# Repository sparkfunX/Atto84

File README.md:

# SparkX Atto84

The Atto84 is an Arduino compatible ATtiny84 breakout pre-programmed with the [Micronucleus V-USB bootloader](https://github.com/micronucleus/micronucleus). The Atto84 Arduino board profile is built around v1.1.5 of SpenceKonde's excellent [ATTinyCore](https://github.com/SpenceKonde/ATTinyCore). 
<br><br>
You can buy one [here](https://sparkle.sparkfun.com/sparkle/storefront_products/14804)!

Documentation
--------------
* **[Hookup Guide](https://learn.sparkfun.com/tutorials/atto84-hookup-guide)** - Basic hookup guide for the Atto84.

License Information
-------------------

This product is _**open source**_! 

Please review the LICENSE.md file for license information. 

If you have any questions or concerns on licensing, please contact techsupport@sparkfun.com.

Distributed as-is; no warranty is given.

- Your friends at SparkFun.

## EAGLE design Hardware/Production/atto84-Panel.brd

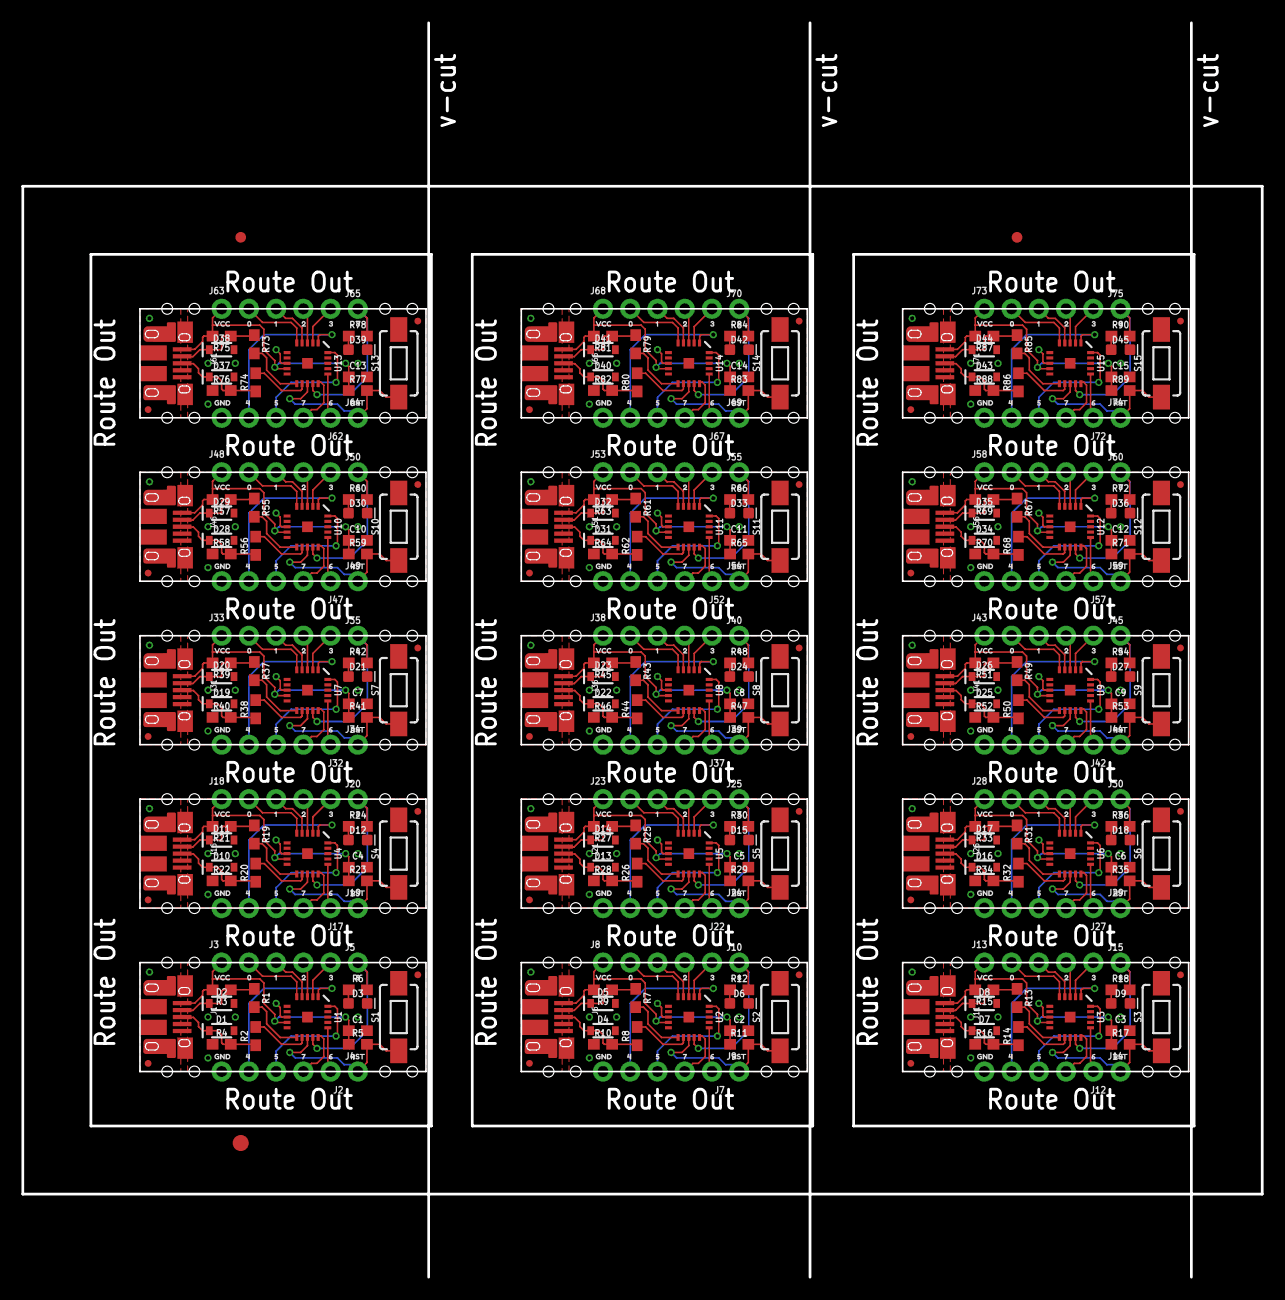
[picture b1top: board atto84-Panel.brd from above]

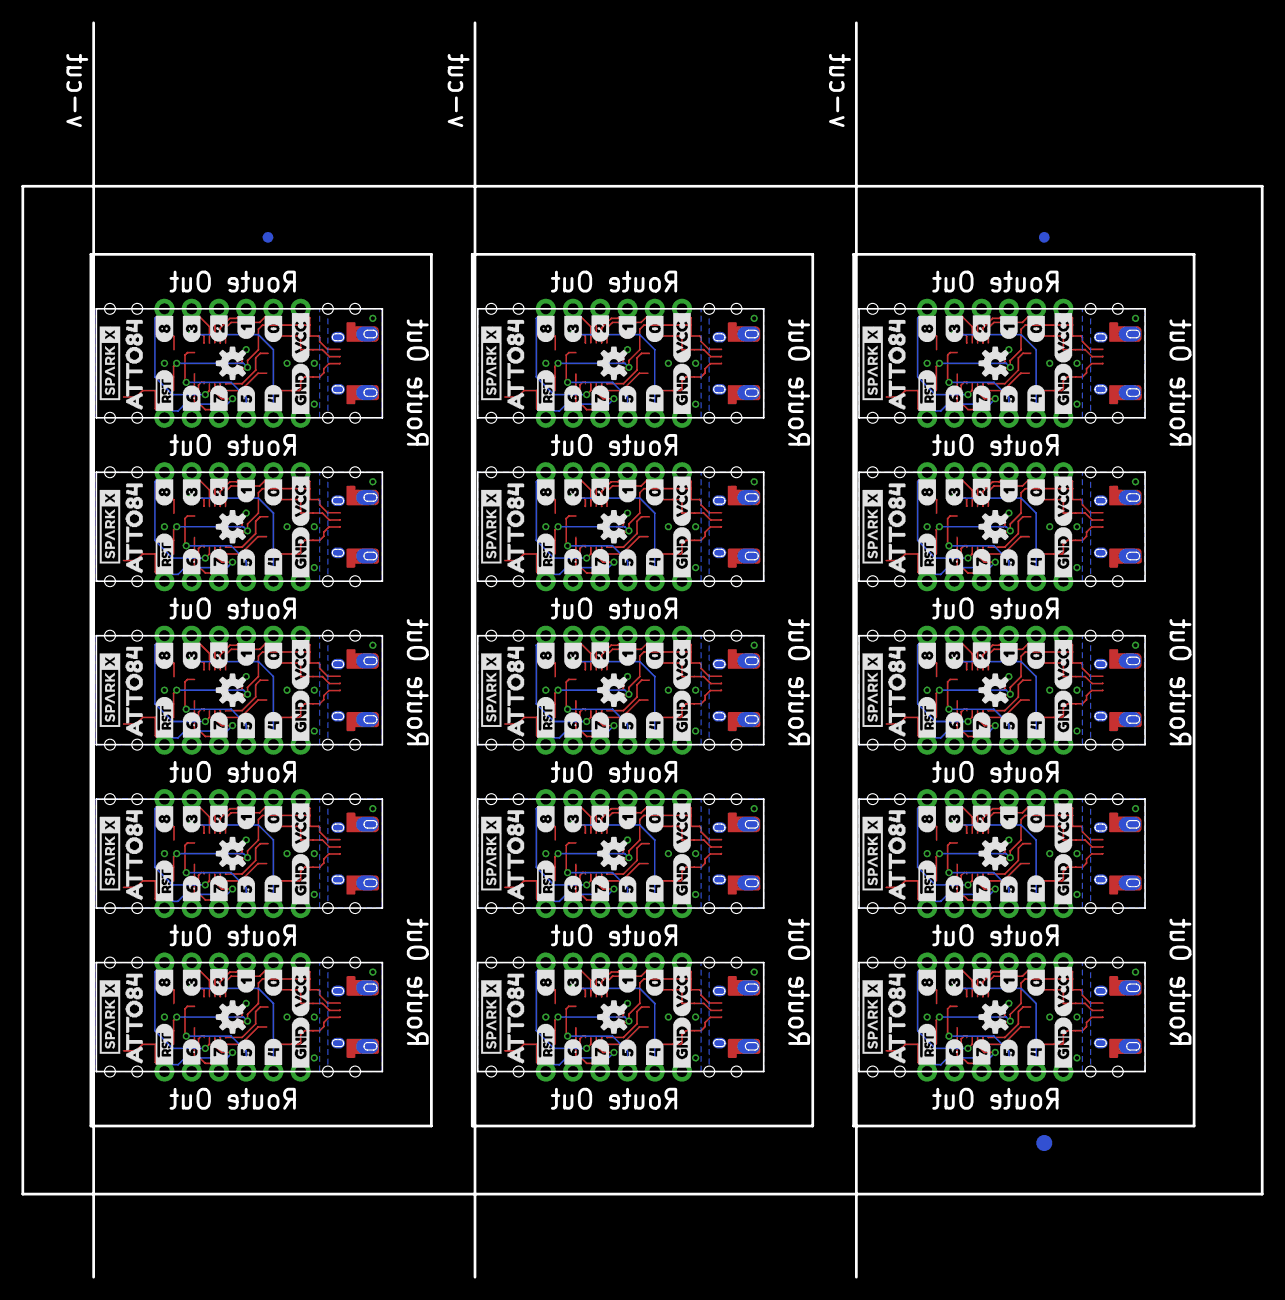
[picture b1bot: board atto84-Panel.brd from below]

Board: 2 copper layers, 115.6 x 94.0 mm, 696 parts (228 on the bottom side), 270 nets.

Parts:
C1, C2, C3, C4, C5, C6, C7, C8, C9, C10, C11, C12, C13, C14, C15: 0.1uF; 0603
D1, D2, D4, D5, D7, D8, D10, D11, D13, D14, D16, D17, D19, D20, D22, D23, D25, D26, D28, D29, D31, D32, D34, D35, D37, D38, D40, D41, D43, D44: 3.6V; SOD-323
D3, D6, D9, D12, D15, D18, D21, D24, D27, D30, D33, D36, D39, D42, D45: BLUE; LED-0603
E$1, E$2, E$3, E$4: FIDUCIAL-1X2
E$5, E$6: FIDUCIAL-1.5X3
FD1, FD2, FD3, FD4, FD5, FD6, FD7, FD8, FD9, FD10, FD11, FD12, FD13, FD14, FD15, FD16, FD17, FD18, FD19, FD20, FD21, FD22, FD23, FD24, FD25, FD26, FD27, FD28, FD29, FD30: FIDUCIALUFIDUCIAL; FIDUCIAL-MICRO
J1, J6, J11, J16, J21, J26, J31, J36, J41, J46, J51, J56, J61, J66, J71: USB-MICROB-PTH-MILL
J2, J3, J7, J8, J12, J13, J17, J18, J22, J23, J27, J28, J32, J33, J37, J38, J42, J43, J47, J48, J52, J53, J57, J58, J62, J63, J67, J68, J72, J73: 1X05_NO_SILK
J4, J5, J9, J10, J14, J15, J19, J20, J24, J25, J29, J30, J34, J35, J39, J40, J44, J45, J49, J50, J54, J55, J59, J60, J64, J65, J69, J70, J74, J75: 1X01_NO_SILK
R1, R2, R7, R8, R13, R14, R19, R20, R25, R26, R31, R32, R37, R38, R43, R44, R49, R50, R55, R56, R61, R62, R67, R68, R73, R74, R79, R80, R85, R86: 68OHM-0603-1/10W-1%; 0603
R3, R9, R15, R21, R27, R33, R39, R45, R51, R57, R63, R69, R75, R81, R87: 1.5k; 0603
R4, R10, R16, R22, R28, R34, R40, R46, R52, R58, R64, R70, R76, R82, R88: 1M; 0603
R5, R11, R17, R23, R29, R35, R41, R47, R53, R59, R65, R71, R77, R83, R89: 10k; 0603
R6, R12, R18, R24, R30, R36, R42, R48, R54, R60, R66, R72, R78, R84, R90: 1k; 0603
S1, S2, S3, S4, S5, S6, S7, S8, S9, S10, S11, S12, S13, S14, S15: TACTILE_SWITCH_SMD_6.0X3.5MM
U1, U2, U3, U4, U5, U6, U7, U8, U9, U10, U11, U12, U13, U14, U15: ATTINY84ATTINY84-20MU; QFN20
U$1, U$28, U$55, U$82, U$109, U$136, U$163, U$190, U$217, U$244, U$271, U$298, U$325, U$352, U$379: 00
U$2, U$29, U$56, U$83, U$110, U$137, U$164, U$191, U$218, U$245, U$272, U$299, U$326, U$353, U$380: 11
U$3, U$30, U$57, U$84, U$111, U$138, U$165, U$192, U$219, U$246, U$273, U$300, U$327, U$354, U$381: 22
U$4, U$31, U$58, U$85, U$112, U$139, U$166, U$193, U$220, U$247, U$274, U$301, U$328, U$355, U$382: 33
U$5, U$32, U$59, U$86, U$113, U$140, U$167, U$194, U$221, U$248, U$275, U$302, U$329, U$356, U$383: 44
U$6, U$33, U$60, U$87, U$114, U$141, U$168, U$195, U$222, U$249, U$276, U$303, U$330, U$357, U$384: 55
U$7, U$34, U$61, U$88, U$115, U$142, U$169, U$196, U$223, U$250, U$277, U$304, U$331, U$358, U$385: 66
U$8, U$35, U$62, U$89, U$116, U$143, U$170, U$197, U$224, U$251, U$278, U$305, U$332, U$359, U$386: 77
U$9, U$36, U$63, U$90, U$117, U$144, U$171, U$198, U$225, U$252, U$279, U$306, U$333, U$360, U$387: RST8
U$10, U$37, U$64, U$91, U$118, U$145, U$172, U$199, U$226, U$253, U$280, U$307, U$334, U$361, U$388: VCC10
U$11, U$38, U$65, U$92, U$119, U$146, U$173, U$200, U$227, U$254, U$281, U$308, U$335, U$362, U$389: GND9
U$12, U$39, U$66, U$93, U$120, U$147, U$174, U$201, U$228, U$255, U$282, U$309, U$336, U$363, U$390: 81
U$13, U$40, U$67, U$94, U$121, U$148, U$175, U$202, U$229, U$256, U$283, U$310, U$337, U$364, U$391: ATTO8411
U$14, U$41, U$68, U$95, U$122, U$149, U$176, U$203, U$230, U$257, U$284, U$311, U$338, U$365, U$392: SPARKX-SMALL
U$15, U$49, U$76, U$103, U$130, U$157, U$184, U$211, U$238, U$265, U$292, U$319, U$346, U$373, U$400: _#RST0
U$16, U$50, U$77, U$104, U$131, U$158, U$185, U$212, U$239, U$266, U$293, U$320, U$347, U$374, U$401: _42
U$17, U$51, U$78, U$105, U$132, U$159, U$186, U$213, U$240, U$267, U$294, U$321, U$348, U$375, U$402: _53
U$18, U$52, U$79, U$106, U$133, U$160, U$187, U$214, U$241, U$268, U$295, U$322, U$349, U$376, U$403: _64
U$19, U$53, U$80, U$107, U$134, U$161, U$188, U$215, U$242, U$269, U$296, U$323, U$350, U$377, U$404: _75
U$20, U$54, U$81, U$108, U$135, U$162, U$189, U$216, U$243, U$270, U$297, U$324, U$351, U$378, U$405: _GND1
U$21, U$42, U$69, U$96, U$123, U$150, U$177, U$204, U$231, U$258, U$285, U$312, U$339, U$366, U$393: VCC_5
U$22, U$43, U$70, U$97, U$124, U$151, U$178, U$205, U$232, U$259, U$286, U$313, U$340, U$367, U$394: 0_4
U$23, U$44, U$71, U$98, U$125, U$152, U$179, U$206, U$233, U$260, U$287, U$314, U$341, U$368, U$395: 1_3
U$24, U$45, U$72, U$99, U$126, U$153, U$180, U$207, U$234, U$261, U$288, U$315, U$342, U$369, U$396: 2_2
U$25, U$46, U$73, U$100, U$127, U$154, U$181, U$208, U$235, U$262, U$289, U$316, U$343, U$370, U$397: 3_1
U$26, U$47, U$74, U$101, U$128, U$155, U$182, U$209, U$236, U$263, U$290, U$317, U$344, U$371, U$398: 8_0
U$27, U$48, U$75, U$102, U$129, U$156, U$183, U$210, U$237, U$264, U$291, U$318, U$345, U$372, U$399: OSHW-LOGO-S

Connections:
!RESET: J4.1, R5.2, S1.1, U1.13
!RESET1: J9.1, R11.2, S2.1, U2.13
!RESET2: J14.1, R17.2, S3.1, U3.13
!RESET3: J19.1, R23.2, S4.1, U4.13
!RESET4: J24.1, R29.2, S5.1, U5.13
!RESET5: J29.1, R35.2, S6.1, U6.13
!RESET6: J34.1, R41.2, S7.1, U7.13
!RESET7: J39.1, R47.2, S8.1, U8.13
!RESET8: J44.1, R53.2, S9.1, U9.13
!RESET9: J49.1, R59.2, S10.1, U10.13
!RESET10: J54.1, R65.2, S11.1, U11.13
!RESET11: J59.1, R71.2, S12.1, U12.13
!RESET12: J64.1, R77.2, S13.1, U13.13
!RESET13: J69.1, R83.2, S14.1, U14.13
!RESET14: J74.1, R89.2, S15.1, U15.13
D0: J3.2, U1.5
D1: J3.3, U1.4
D2: J3.4, U1.3
D3: J3.5, U1.2
D4: J2.4, U1.1
D5: J2.3, U1.20
D6: J2.1, U1.16
D7: J2.2, U1.15
D8: J8.2, U2.5
D9: J8.3, U2.4
D10: J8.4, U2.3
D11: J8.5, U2.2
D12: J7.4, U2.1
D13: J7.3, U2.20
D14: J7.1, U2.16
D15: J7.2, U2.15
D16: J13.2, U3.5
D17: J13.3, U3.4
D18: J13.4, U3.3
D19: J13.5, U3.2
D20: J12.4, U3.1
D21: J12.3, U3.20
D22: J12.1, U3.16
D23: J12.2, U3.15
D24: J18.2, U4.5
D25: J18.3, U4.4
D26: J18.4, U4.3
D27: J18.5, U4.2
D28: J17.4, U4.1
D29: J17.3, U4.20
D30: J17.1, U4.16
D31: J17.2, U4.15
D32: J23.2, U5.5
D33: J23.3, U5.4
D34: J23.4, U5.3
D35: J23.5, U5.2
D36: J22.4, U5.1
D37: J22.3, U5.20
D38: J22.1, U5.16
D39: J22.2, U5.15
D40: J28.2, U6.5
D41: J28.3, U6.4
D42: J28.4, U6.3
D43: J28.5, U6.2
D44: J27.4, U6.1
D45: J27.3, U6.20
D46: J27.1, U6.16
D47: J27.2, U6.15
D48: J33.2, U7.5
D49: J33.3, U7.4
D50: J33.4, U7.3
D51: J33.5, U7.2
D52: J32.4, U7.1
D53: J32.3, U7.20
D54: J32.1, U7.16
D55: J32.2, U7.15
D56: J38.2, U8.5
D57: J38.3, U8.4
D58: J38.4, U8.3
D59: J38.5, U8.2
D60: J37.4, U8.1
D61: J37.3, U8.20
D62: J37.1, U8.16
D63: J37.2, U8.15
D64: J43.2, U9.5
D65: J43.3, U9.4
D66: J43.4, U9.3
D67: J43.5, U9.2
D68: J42.4, U9.1
D69: J42.3, U9.20
D70: J42.1, U9.16
D71: J42.2, U9.15
D72: J48.2, U10.5
D73: J48.3, U10.4
D74: J48.4, U10.3
D75: J48.5, U10.2
D76: J47.4, U10.1
D77: J47.3, U10.20
D78: J47.1, U10.16
D79: J47.2, U10.15
D80: J53.2, U11.5
D81: J53.3, U11.4
D82: J53.4, U11.3
D83: J53.5, U11.2
D84: J52.4, U11.1
D85: J52.3, U11.20
D86: J52.1, U11.16
D87: J52.2, U11.15
D88: J58.2, U12.5
D89: J58.3, U12.4
D90: J58.4, U12.3
D91: J58.5, U12.2
D92: J57.4, U12.1
D93: J57.3, U12.20
D94: J57.1, U12.16
D95: J57.2, U12.15
D96: J63.2, U13.5
D97: J63.3, U13.4
D98: J63.4, U13.3
D99: J63.5, U13.2
D100: J62.4, U13.1
D101: J62.3, U13.20
D102: J62.1, U13.16
D103: J62.2, U13.15
D104: J68.2, U14.5
D105: J68.3, U14.4
D106: J68.4, U14.3
D107: J68.5, U14.2
D108: J67.4, U14.1
D109: J67.3, U14.20
D110: J67.1, U14.16
D111: J67.2, U14.15
D112: J73.2, U15.5
D113: J73.3, U15.4
D114: J73.4, U15.3
D115: J73.5, U15.2
D116: J72.4, U15.1
D117: J72.3, U15.20
D118: J72.1, U15.16
D119: J72.2, U15.15
D+: D1.C, J1.D+, R2.1, R4.2
D+1: D4.C, J6.D+, R8.1, R10.2
D+2: D7.C, J11.D+, R14.1, R16.2
D+3: D10.C, J16.D+, R20.1, R22.2
D+4: D13.C, J21.D+, R26.1, R28.2
D+5: D16.C, J26.D+, R32.1, R34.2
D+6: D19.C, J31.D+, R38.1, R40.2
D+7: D22.C, J36.D+, R44.1, R46.2
D+8: D25.C, J41.D+, R50.1, R52.2
D+9: D28.C, J46.D+, R56.1, R58.2
D+10: D31.C, J51.D+, R62.1, R64.2
D+11: D34.C, J56.D+, R68.1, R70.2
D+12: D37.C, J61.D+, R74.1, R76.2
D+13: D40.C, J66.D+, R80.1, R82.2
D+14: D43.C, J71.D+, R86.1, R88.2
D-: D2.C, J1.D-, R1.1, R3.1
D-1: D5.C, J6.D-, R7.1, R9.1
D-2: D8.C, J11.D-, R13.1, R15.1
D-3: D11.C, J16.D-, R19.1, R21.1
D-4: D14.C, J21.D-, R25.1, R27.1
D-5: D17.C, J26.D-, R31.1, R33.1
D-6: D20.C, J31.D-, R37.1, R39.1
D-7: D23.C, J36.D-, R43.1, R45.1
D-8: D26.C, J41.D-, R49.1, R51.1
D-9: D29.C, J46.D-, R55.1, R57.1
D-10: D32.C, J51.D-, R61.1, R63.1
D-11: D35.C, J56.D-, R67.1, R69.1
D-12: D38.C, J61.D-, R73.1, R75.1
D-13: D41.C, J66.D-, R79.1, R81.1
D-14: D44.C, J71.D-, R85.1, R87.1
GND: C1.2, D1.A, D2.A, D3.C, J1.GND, J2.5, R4.1, S1.2, U1.8
GND1: C2.2, D4.A, D5.A, D6.C, J6.GND, J7.5, R10.1, S2.2, U2.8
GND2: C3.2, D7.A, D8.A, D9.C, J11.GND, J12.5, R16.1, S3.2, U3.8
GND3: C4.2, D10.A, D11.A, D12.C, J16.GND, J17.5, R22.1, S4.2, U4.8
GND4: C5.2, D13.A, D14.A, D15.C, J21.GND, J22.5, R28.1, S5.2, U5.8
GND5: C6.2, D16.A, D17.A, D18.C, J26.GND, J27.5, R34.1, S6.2, U6.8
GND6: C7.2, D19.A, D20.A, D21.C, J31.GND, J32.5, R40.1, S7.2, U7.8
GND7: C8.2, D22.A, D23.A, D24.C, J36.GND, J37.5, R46.1, S8.2, U8.8
GND8: C9.2, D25.A, D26.A, D27.C, J41.GND, J42.5, R52.1, S9.2, U9.8
GND9: C10.2, D28.A, D29.A, D30.C, J46.GND, J47.5, R58.1, S10.2, U10.8
GND10: C11.2, D31.A, D32.A, D33.C, J51.GND, J52.5, R64.1, S11.2, U11.8
GND11: C12.2, D34.A, D35.A, D36.C, J56.GND, J57.5, R70.1, S12.2, U12.8
GND12: C13.2, D37.A, D38.A, D39.C, J61.GND, J62.5, R76.1, S13.2, U13.8
GND13: C14.2, D40.A, D41.A, D42.C, J66.GND, J67.5, R82.1, S14.2, U14.8
GND14: C15.2, D43.A, D44.A, D45.C, J71.GND, J72.5, R88.1, S15.2, U15.8
unnamed: D6.A, R12.1
unnamed: D9.A, R18.1
unnamed: D3.A, R6.1
unnamed: D12.A, R24.1
unnamed: D15.A, R30.1
unnamed: D18.A, R36.1
unnamed: D21.A, R42.1
unnamed: D24.A, R48.1
unnamed: D27.A, R54.1
unnamed: D30.A, R60.1
unnamed: D33.A, R66.1
unnamed: D36.A, R72.1
unnamed: D39.A, R78.1
unnamed: D42.A, R84.1
unnamed: D45.A, R90.1
PB0: R1.2, U1.11
PB1: R2.2, U1.12
PB2: R7.2, U2.11
PB3: R8.2, U2.12
PB4: R13.2, U3.11
PB5: R14.2, U3.12
PB6: R19.2, U4.11
PB7: R20.2, U4.12
PB8: R25.2, U5.11
PB9: R26.2, U5.12
PB10: R31.2, U6.11
PB11: R32.2, U6.12
PB12: R37.2, U7.11
PB13: R38.2, U7.12
PB14: R43.2, U8.11
PB15: R44.2, U8.12
PB16: R49.2, U9.11
PB17: R50.2, U9.12
PB18: R55.2, U10.11
PB19: R56.2, U10.12
PB20: R61.2, U11.11
PB21: R62.2, U11.12
PB22: R67.2, U12.11
PB23: R68.2, U12.12
PB24: R73.2, U13.11
PB25: R74.2, U13.12
PB26: R79.2, U14.11
PB27: R80.2, U14.12
PB28: R85.2, U15.11
PB29: R86.2, U15.12
SHLD: J1.SHIELD, J1.SHIELD2, J1.SHIELD3, J1.SHIELD4, J1.SHIELD5, J1.SHIELD6, J1.SHIELD7, J1.SHIELD8, J1.SHIELD9, J1.SHIELD10
SHLD1: J6.SHIELD, J6.SHIELD2, J6.SHIELD3, J6.SHIELD4, J6.SHIELD5, J6.SHIELD6, J6.SHIELD7, J6.SHIELD8, J6.SHIELD9, J6.SHIELD10
SHLD2: J11.SHIELD, J11.SHIELD2, J11.SHIELD3, J11.SHIELD4, J11.SHIELD5, J11.SHIELD6, J11.SHIELD7, J11.SHIELD8, J11.SHIELD9, J11.SHIELD10
SHLD3: J16.SHIELD, J16.SHIELD2, J16.SHIELD3, J16.SHIELD4, J16.SHIELD5, J16.SHIELD6, J16.SHIELD7, J16.SHIELD8, J16.SHIELD9, J16.SHIELD10
SHLD4: J21.SHIELD, J21.SHIELD2, J21.SHIELD3, J21.SHIELD4, J21.SHIELD5, J21.SHIELD6, J21.SHIELD7, J21.SHIELD8, J21.SHIELD9, J21.SHIELD10
SHLD5: J26.SHIELD, J26.SHIELD2, J26.SHIELD3, J26.SHIELD4, J26.SHIELD5, J26.SHIELD6, J26.SHIELD7, J26.SHIELD8, J26.SHIELD9, J26.SHIELD10
SHLD6: J31.SHIELD, J31.SHIELD2, J31.SHIELD3, J31.SHIELD4, J31.SHIELD5, J31.SHIELD6, J31.SHIELD7, J31.SHIELD8, J31.SHIELD9, J31.SHIELD10
SHLD7: J36.SHIELD, J36.SHIELD2, J36.SHIELD3, J36.SHIELD4, J36.SHIELD5, J36.SHIELD6, J36.SHIELD7, J36.SHIELD8, J36.SHIELD9, J36.SHIELD10
SHLD8: J41.SHIELD, J41.SHIELD2, J41.SHIELD3, J41.SHIELD4, J41.SHIELD5, J41.SHIELD6, J41.SHIELD7, J41.SHIELD8, J41.SHIELD9, J41.SHIELD10
SHLD9: J46.SHIELD, J46.SHIELD2, J46.SHIELD3, J46.SHIELD4, J46.SHIELD5, J46.SHIELD6, J46.SHIELD7, J46.SHIELD8, J46.SHIELD9, J46.SHIELD10
SHLD10: J51.SHIELD, J51.SHIELD2, J51.SHIELD3, J51.SHIELD4, J51.SHIELD5, J51.SHIELD6, J51.SHIELD7, J51.SHIELD8, J51.SHIELD9, J51.SHIELD10
SHLD11: J56.SHIELD, J56.SHIELD2, J56.SHIELD3, J56.SHIELD4, J56.SHIELD5, J56.SHIELD6, J56.SHIELD7, J56.SHIELD8, J56.SHIELD9, J56.SHIELD10
SHLD12: J61.SHIELD, J61.SHIELD2, J61.SHIELD3, J61.SHIELD4, J61.SHIELD5, J61.SHIELD6, J61.SHIELD7, J61.SHIELD8, J61.SHIELD9, J61.SHIELD10
SHLD13: J66.SHIELD, J66.SHIELD2, J66.SHIELD3, J66.SHIELD4, J66.SHIELD5, J66.SHIELD6, J66.SHIELD7, J66.SHIELD8, J66.SHIELD9, J66.SHIELD10
SHLD14: J71.SHIELD, J71.SHIELD2, J71.SHIELD3, J71.SHIELD4, J71.SHIELD5, J71.SHIELD6, J71.SHIELD7, J71.SHIELD8, J71.SHIELD9, J71.SHIELD10
STATUS: J5.1, R6.2, U1.14
STATUS1: J10.1, R12.2, U2.14
STATUS2: J15.1, R18.2, U3.14
STATUS3: J20.1, R24.2, U4.14
STATUS4: J25.1, R30.2, U5.14
STATUS5: J30.1, R36.2, U6.14
STATUS6: J35.1, R42.2, U7.14
STATUS7: J40.1, R48.2, U8.14
STATUS8: J45.1, R54.2, U9.14
STATUS9: J50.1, R60.2, U10.14
STATUS10: J55.1, R66.2, U11.14
STATUS11: J60.1, R72.2, U12.14
STATUS12: J65.1, R78.2, U13.14
STATUS13: J70.1, R84.2, U14.14
STATUS14: J75.1, R90.2, U15.14
VCC: C1.1, J1.VBUS, J3.1, R3.2, R5.1, U1.9
VCC1: C2.1, J6.VBUS, J8.1, R9.2, R11.1, U2.9
VCC2: C3.1, J11.VBUS, J13.1, R15.2, R17.1, U3.9
VCC3: C4.1, J16.VBUS, J18.1, R21.2, R23.1, U4.9
VCC4: C5.1, J21.VBUS, J23.1, R27.2, R29.1, U5.9
VCC5: C6.1, J26.VBUS, J28.1, R33.2, R35.1, U6.9
VCC6: C7.1, J31.VBUS, J33.1, R39.2, R41.1, U7.9
VCC7: C8.1, J36.VBUS, J38.1, R45.2, R47.1, U8.9
VCC8: C9.1, J41.VBUS, J43.1, R51.2, R53.1, U9.9
VCC9: C10.1, J46.VBUS, J48.1, R57.2, R59.1, U10.9
VCC10: C11.1, J51.VBUS, J53.1, R63.2, R65.1, U11.9
VCC11: C12.1, J56.VBUS, J58.1, R69.2, R71.1, U12.9
VCC12: C13.1, J61.VBUS, J63.1, R75.2, R77.1, U13.9
VCC13: C14.1, J66.VBUS, J68.1, R81.2, R83.1, U14.9
VCC14: C15.1, J71.VBUS, J73.1, R87.2, R89.1, U15.9

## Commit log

2018-06-25 Adding tested bootloader build
    Freezing my production environment in amber here:
    avrdude bin and conf borrowed from Arduino 1.8.5
    batch file burns bootloaders with arduinoISP
    t84_default built with sparkfun attiny PID/VID
2018-06-26 Adding Pinout Diagram
2018-06-27 ABC
    Always
2018-08-16 Pushing "new" version

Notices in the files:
parts and their libraries:
SparkFun-Capacitors: Licensing: Creative Commons ShareAlike 4.0 International - https://creativecommons.org/licenses/by-sa/4.0
